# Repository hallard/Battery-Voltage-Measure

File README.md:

# Battery Voltage monitor with no current drain breakout board

Based on previous couple of [voltage divider break out](https://github.com/hallard/R-Divider-Breakout) for ADS1015 ADC board, I needed a simple board being agble to measure battery voltage without draining battery current.
For this I created this little basic board. It's just a basic resistor divider whith a mosfet to enable the measure so it does not drain any current from battery when not enabled. Measure is done using a analog entry of the micro controller (arduino, STM32, ESP8266, ESP32, ...)

## Detailed Description

You only need 3 or 4 wires depending on what you need to achieve

- VBat (connected to + of the battery)
- GND  (connected to - of the battery)
- AN is the analog entry to measure voltage 
- EN is the enable pin

To enable the divider to work, you need to set the EN pin to 0. Leaving this pin floating will disable the divider since there is a pullup on the transistor gate.

Take care of the max voltage value of your analog input pin, some have limited value (IE ESP8266)

Voltage on analog pin (when enabled) is VBat * ( R2 / (R1 + R2) ), so with R1=10K and R2=10K voltage is VBat * 0.5. So 4.2V VBat means 2.1V on analog pin. In this case, with 3.3V devices, it can go up to 6.6V
If you need to divide more increase top resistor value example R1=20K, R2=10K you can go up to 9.9V.
Check Voltage Divider online calculator like this [one][10] or this [one][11] if needed

If you don't want to use enable pin, put some solder paste on JP1 to short the pasd, leave Q1 and R3 unpopulated and you have a basic divider. 
In this case to avoid battery drain (that will occurs every time), increase resistors values (470K + 470K for example)

## Schematic

Q1 can be any SOT23 P-Mosfet so BSS84, BS250, ... are fine. Resistors are 0805 package.

## Boards 

&nbsp;&nbsp;

You can order the PCB of this board at [PCBs.io][3]. PCBs.io give me some reward when you order my designed boards from their site. This is pretty good, because I can use these rewards to create and design new boards and order them for free, so if you don't care about PCB manufacturer please use [PCBs.io][3].

## License

You can do whatever you like with this design.

## Misc

See news and other projects on my [blog][2] 
 
[2]: https://hallard.me
[3]: https://PCBs.io/share/zjqg5 
[10]: http://www.ohmslawcalculator.com/voltage-divider-calculator
[11]: http://www.ti.com/download/kbase/volt/volt_div3.htm

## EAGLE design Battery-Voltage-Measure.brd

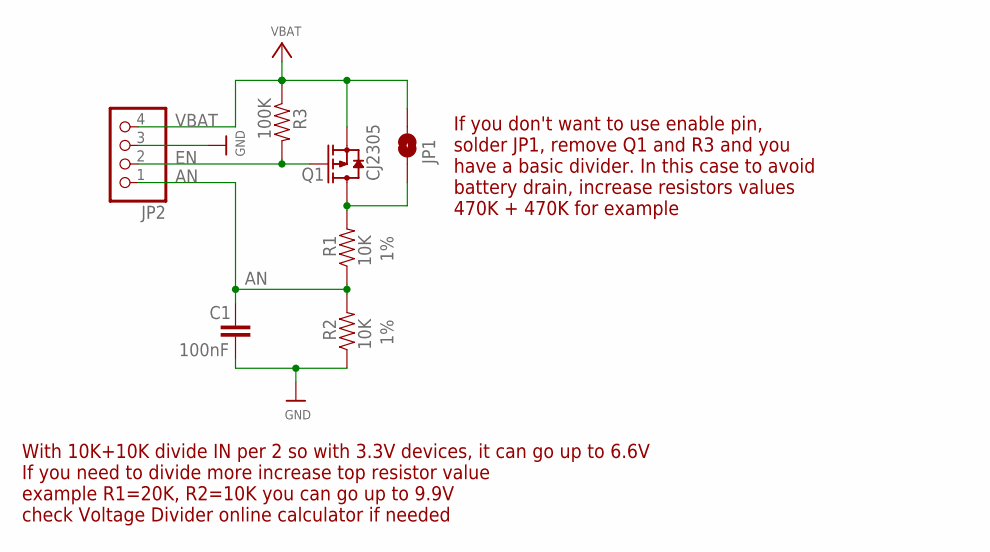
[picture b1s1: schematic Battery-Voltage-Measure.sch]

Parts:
C1: 100nF; 0805-CAP
JP1: JUMPER-SMT_2_NO_SILK; SMT-JUMPER_2_NO_SILK
JP2: HEADER-1X476MIL; 1X04_ROUND_76
Q1: CJ2305; SOT23
R1, R2: 10K; 0805-RES
R3: 100K; 0805-RES

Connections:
AN: C1.1, JP2.1, R1.1, R2.2
EN: JP2.2, Q1.1 (G), R3.2
GND: C1.2, JP2.3, R2.1
IN0: JP1.1, Q1.3 (D), R1.2
VBAT: JP1.2, JP2.4, Q1.2 (S), R3.1

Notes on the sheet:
With 10K+10K divide IN per 2 so with 3.3V devices, it can go up to 6.6V If you need to divide more increase top resistor value example R1=20K, R2=10K you can go up to 9.9V check Voltage Divider online calculator if needed
If you don't want to use enable pin, solder JP1, remove Q1 and R3 and you have a basic divider. In this case to avoid battery drain, increase resistors values 470K + 470K for example

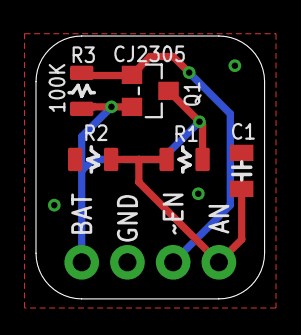
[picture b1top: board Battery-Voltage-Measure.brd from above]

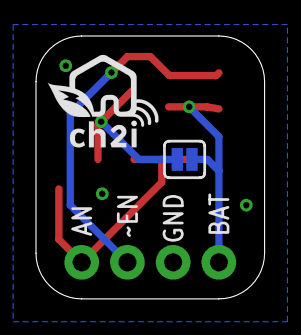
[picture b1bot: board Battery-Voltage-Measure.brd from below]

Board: 2 copper layers, 12.7 x 14.6 mm, 8 parts (2 on the bottom side), 5 nets.

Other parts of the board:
U$5: LOGO_C2I_015

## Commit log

2018-04-15 :circus_tent: Added .gitattributes
2018-04-15 Creation
2018-04-15 Fixed link
2018-04-15 cosmetic
2018-04-15 saved
2018-04-15 Transistor description
2018-04-15 Zommed
2018-04-15 Doc on divider

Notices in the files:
parts and their libraries:
SparkFun-Jumpers: Licensing: Creative Commons ShareAlike 4.0 International - https://creativecommons.org/licenses/by-sa/4.0
